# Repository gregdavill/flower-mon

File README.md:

# Zigbee Plant Watering Sensor

New circuit board layout based off the following projects:
 - https://github.com/smartboxchannel/Plant-Watering-Sensor-Zigbee
 - https://github.com/diyruz/flower

Capacitance sensor soil moisture sensor based on the CC2530 SoC.
Designed to communicate over Zigbee to a coordinator.
Powered from a CR2032, optional humidity, and temperature sensors.

## Photo

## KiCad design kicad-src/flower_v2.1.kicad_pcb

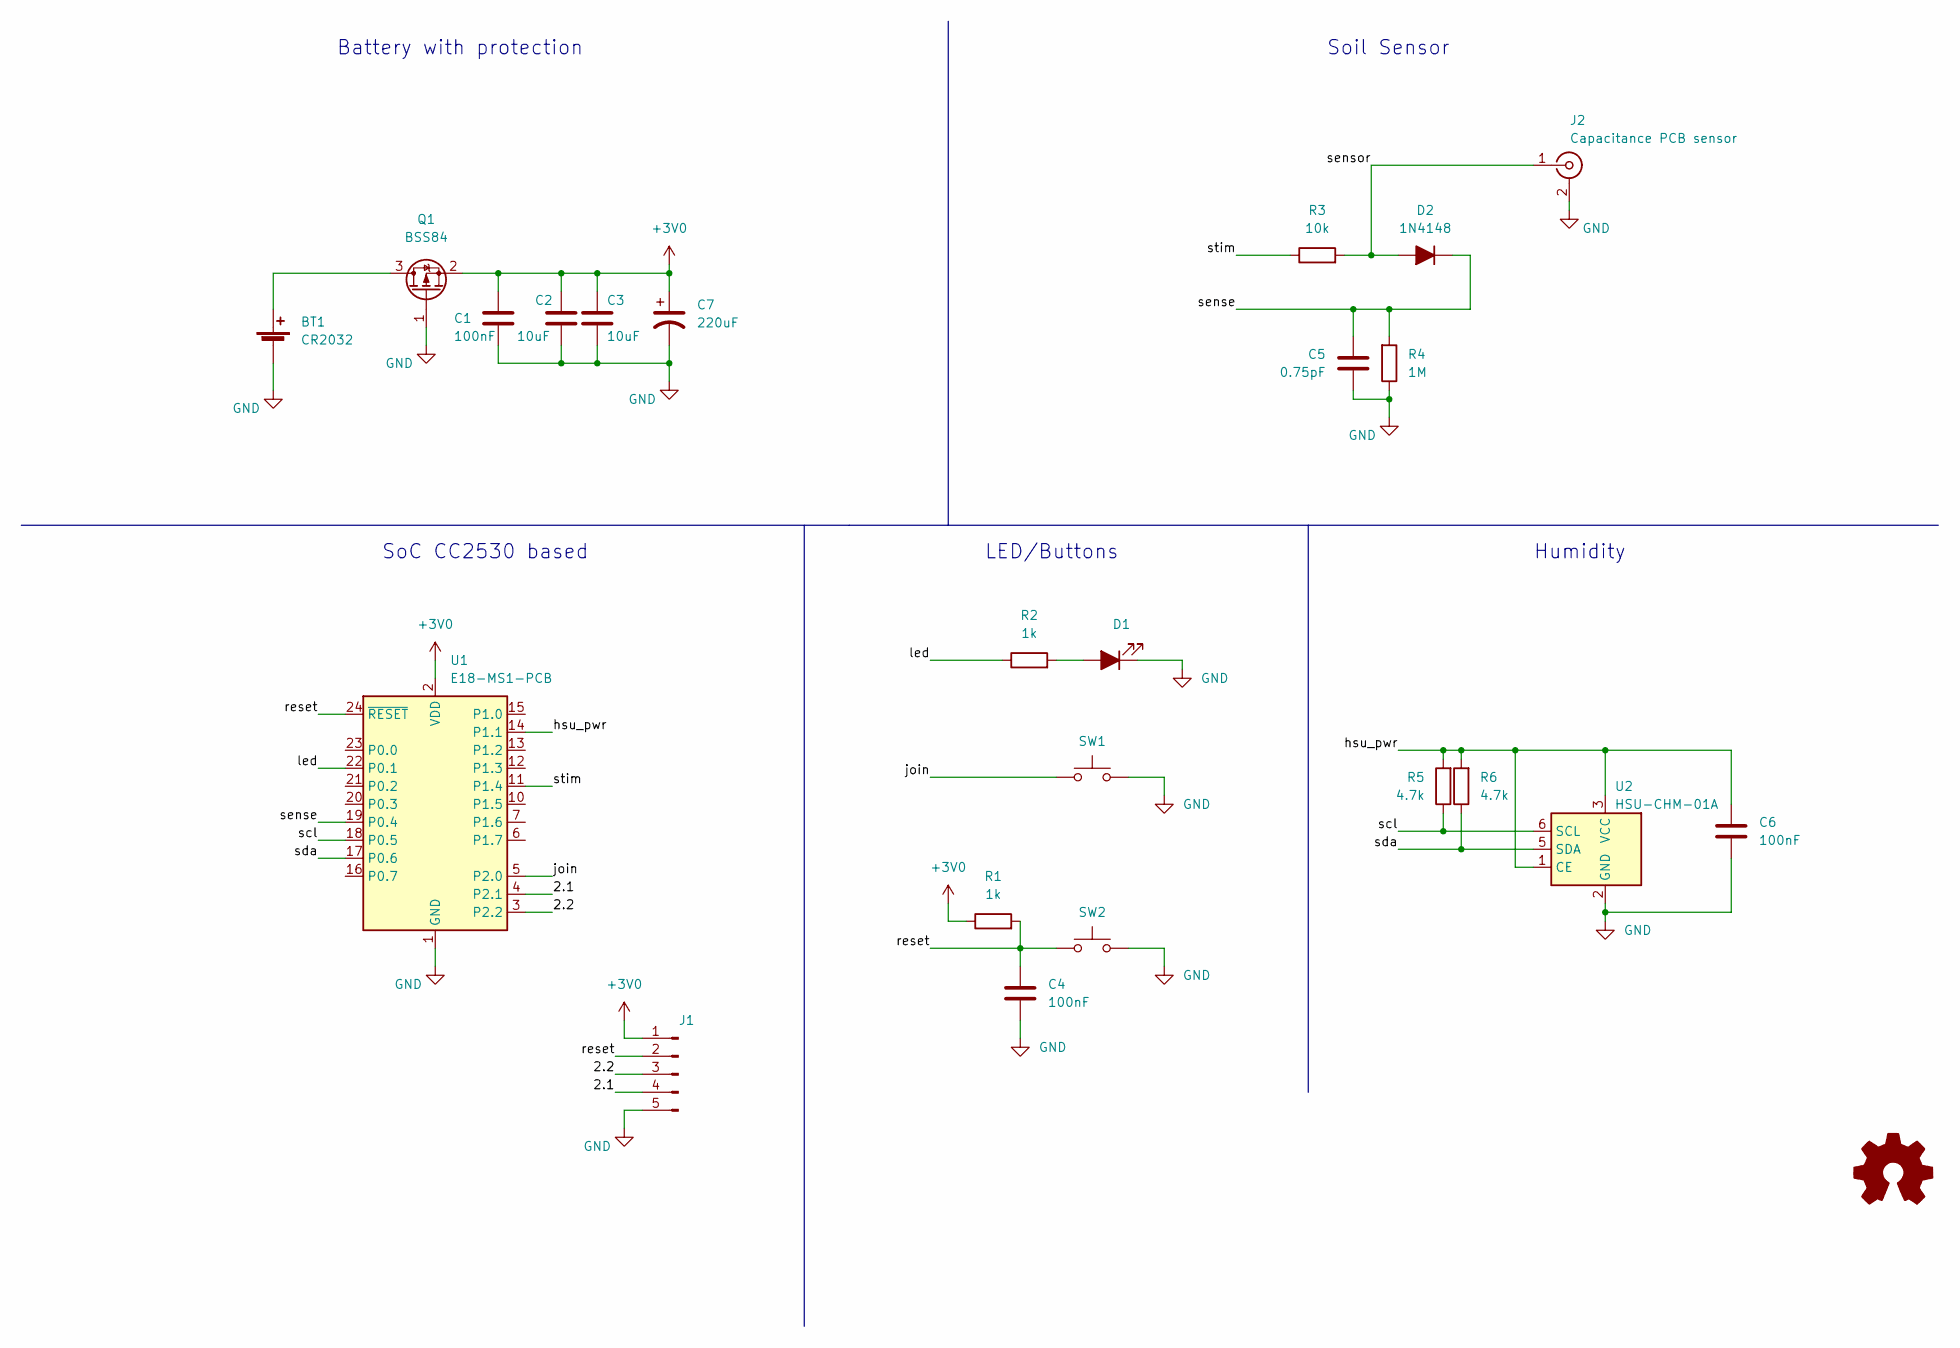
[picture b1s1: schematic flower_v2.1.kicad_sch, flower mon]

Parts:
BT1: CR2032; keystone_1058
C1, C4, C6: 100nF; C_0402_1005Metric
C2, C3: 10uF; C_0603_1608Metric
C5: 0.75pF; C_0402_1005Metric
C7: 220uF; CP_EIA-3528-21_Kemet-B
D1: green; LED_0603_1608Metric
D2: 1N4148; D_SOD-323F
J1: Conn_01x05_Male; PinHeader_1x05_P1.00mm_Vertical
J2: Capacitance PCB sensor
Q1: BSS84; SOT-23
R1, R2: 1k; R_0402_1005Metric
R3: 10k; R_0402_1005Metric
R4: 1M; R_0402_1005Metric
R5, R6: 4.7k; R_0402_1005Metric
SW1, SW2: SW_Push; SW_SPST_PTS810
U1: E18-MS1-PCB
U2: HSU-CHM-01A; DFN-6-1EP_2x2mm_P0.5mm_EP0.61x1.42mm

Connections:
+3V0: C1.1, C2.1, C3.1, C7.1, J1.1, Q1.2 (S), R1.1, U1.2 (VDD)
/2.1: J1.4, U1.4 (P2.1)
/2.2: J1.3, U1.3 (P2.2)
/hsu_pwr: C6.1, R5.2, R6.2, U1.14 (P1.1), U2.1 (CE), U2.3 (VCC)
/join: SW1.1, U1.5 (P2.0)
/led: R2.1, U1.22 (P0.1)
/reset: C4.1, J1.2, R1.2, SW2.1, U1.24 (~RESET)
/scl: R5.1, U1.18 (P0.5), U2.6 (SCL)
/sda: R6.1, U1.17 (P0.6), U2.5 (SDA)
/sense: C5.1, D2.1 (K), R4.2, U1.19 (P0.4)
/sensor: D2.2 (A), J2.1 (In), R3.2
/stim: R3.1, U1.11 (P1.4)
GND: BT1.2 (-), C1.2, C2.2, C3.2, C4.2, C5.2, C6.2, C7.2, D1.1 (K), J1.5, J2.2 (Ext), Q1.1 (G), R4.1, SW1.2, SW2.2, U1.1 (GND), U2.2 (GND)
unnamed: BT1.1 (+), Q1.3 (D)
unnamed: D1.2 (A), R2.2

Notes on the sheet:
Battery with protection
Humidity
SoC CC2530 based
Soil Sensor
LED/Buttons

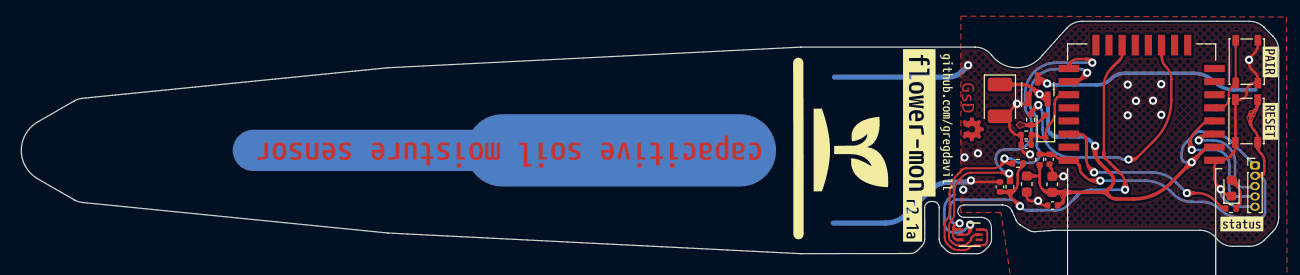
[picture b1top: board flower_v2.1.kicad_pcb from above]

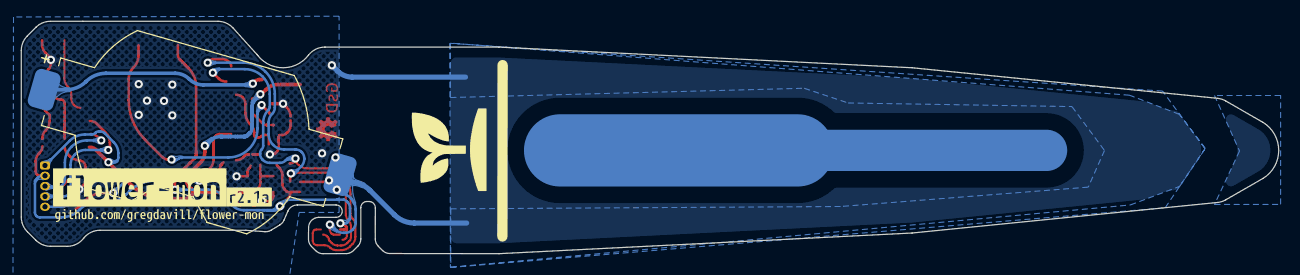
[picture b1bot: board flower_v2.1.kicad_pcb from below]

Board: 2 copper layers, 121.7 x 22.5 mm, 32 parts (4 on the bottom side), 15 nets.

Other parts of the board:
kibuzzard-62A9BF5E: G***; kibuzzard-62A9BF5E
kibuzzard-62A9BF6E: G***; kibuzzard-62A9BF6E
kibuzzard-628C3F80: G***; kibuzzard-628C3F80
kibuzzard-628C3FD2: G***; kibuzzard-628C3FD2
kibuzzard-628C3FDC: G***; kibuzzard-628C3FDC
kibuzzard-628C36A2: G***; kibuzzard-628C36A2
kibuzzard-628C37D3: G***; kibuzzard-628C37D3
kibuzzard-628CB3EE: G***; kibuzzard-628CB3EE
kibuzzard-628D81B8: G***; kibuzzard-628D81B8
kibuzzard-628D81CB: G***; kibuzzard-628D81CB

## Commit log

2022-05-25 Update PCB layout
2022-05-26 Add test CI file
2022-05-26 Update ci
2022-05-27 Add firmware
2022-06-11 Update firmware
    - Fix compile issues by fixing include case
2022-06-11 Update project file
2022-06-12 Revert some Z-Stack src changes
2022-06-13 Update zstack-lib
    - Fix inital battery values on POR
    - Add support for UART debugging with power saving enabled
2022-06-13 Update project files
    - Merge changes from PWS
2022-06-13 Apply fixes to Z-Stack
    - Add event for UART_TX_IDLE
2022-06-13 Z-Stack: PM2 + UART DMA bug fix
2022-06-13 Reduce power consumption
    - The OW data pin was left with a pullup, causing ~100uA of leakage.
2022-06-13 Upidate firmware
    - Rework i2c library to improve speed, and reduce duplicated code
    - Add Humidity readout
    - Rework sensor sample state machine
    - Fix pull-up Enable/Disable polarity
    - Bump report timer to 5m
    - Add support for HSU-CHM-01A Humidity sensor
2022-06-14 Firmware fix PWM output to soil sensor
2022-06-14 Update gitignore
    - Ensure build files aren't included
2022-06-14 fw: fix local/global variable bug
2022-06-14 docs: Add datasheets
2022-06-15 hw2.1a: Fix HSU-CHM footprint
    Fixes #1
2022-06-15 hw2.1a: Fix bugs
    - Added 220uF Tantulum cap, fixes #2
    - Removed DS18B20, fixes #3
    - Updated battery footprint, fixes #4

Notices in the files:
kicad-src/flower_v2.1.kicad_pcb:
OSHW: GPL-3.0
